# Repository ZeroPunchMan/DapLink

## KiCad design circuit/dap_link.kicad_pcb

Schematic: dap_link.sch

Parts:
C1: 10nF; C_0603_1608Metric_Pad1.05x0.95mm_HandSolder
C2: 100nF; C_0603_1608Metric_Pad1.05x0.95mm_HandSolder
C3: 1uF; C_0603_1608Metric_Pad1.05x0.95mm_HandSolder
C4, C7: 10pF; C_0603_1608Metric_Pad1.05x0.95mm_HandSolder
C5: 10uF; CP_EIA-3528-12_Kemet-T_Pad1.50x2.35mm_HandSolder
C6: 22uF; CP_EIA-3528-12_Kemet-T_Pad1.50x2.35mm_HandSolder
C8: 0.1uF; C_0603_1608Metric_Pad1.05x0.95mm_HandSolder
D1: LEDG; LED_0603_1608Metric_Pad1.05x0.95mm_HandSolder
D2: LEDR; LED_0603_1608Metric_Pad1.05x0.95mm_HandSolder
J1: USB_A_CONN; USB_A_CNCTech_1001-011-01101_Horizontal
J2: SWD_CONN_5P; PinHeader_1x05_P2.54mm_Vertical
J3: UART1_CONN_3P; PinHeader_1x03_P2.54mm_Vertical
J4: PAEX_CONN_8P; PinHeader_1x08_P2.54mm_Horizontal
R1: 1M; R_0603_1608Metric_Pad1.05x0.95mm_HandSolder
R2, R3: 22R; R_0603_1608Metric_Pad1.05x0.95mm_HandSolder
R4: 1.5K; R_0603_1608Metric_Pad1.05x0.95mm_HandSolder
R5: 0R; R_0603_1608Metric_Pad1.05x0.95mm_HandSolder
R6, R7: 100R; R_0603_1608Metric_Pad1.05x0.95mm_HandSolder
R8, R9, R11, R13, R14, R15, R16, R17, R18: 1K; R_0603_1608Metric_Pad1.05x0.95mm_HandSolder
R10, R12: 10K; R_0603_1608Metric_Pad1.05x0.95mm_HandSolder
U1: STM32F103CBTx; LQFP-48_7x7mm_P0.5mm
U2: AMS1117-3.3; SOT-223-3_TabPin2
Y1: 8MHz; Crystal_SMD_SeikoEpson_MC405-2Pin_9.6x4.1mm

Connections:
+3V3: C2.2, C3.2, C6.1, D1.2 (A), D2.2 (A), J2.5, R4.1, R10.1, U1.1 (VBAT), U1.9 (VDDA), U1.24 (VDD1), U1.36 (VDD2), U1.48 (VDD3), U2.2 (VO)
/LEDG_GPIO: R8.2, U1.29 (PA8)
/LEDR_GPIO: R9.2, U1.17 (PA7)
/NRST: C8.1, J2.4, R10.2, U1.7 (NRST)
/OSC_IN: C4.1, U1.5 (PD0/OSC_IN), Y1.1
/OSC_OUT: R5.1, U1.6 (PD1/OSC_OUT)
/PA0: R11.1, U1.10 (PA0)
/PA1: R13.1, U1.11 (PA1)
/PA2: R14.1, U1.12 (PA2)
/PA3: R15.1, U1.13 (PA3)
/PA4: R16.1, U1.14 (PA4)
/PA5: R17.1, U1.15 (PA5)
/PA6: R18.1, U1.16 (PA6)
/SWCLK: J2.2, U1.37 (PA14)
/SWDIO: J2.3, U1.34 (PA13)
/URX1: J3.2, R7.1
/USB_D+: R3.1, U1.33 (PA12)
/USB_D-: R2.1, U1.32 (PA11)
/UTX1: J3.3, R6.1
GND: C1.2, C2.1, C3.1, C4.2, C5.2, C6.2, C7.2, C8.2, J1.4 (GND), J2.1, J3.1, J4.1, R1.2, R12.2, U1.8 (VSSA), U1.23 (VSS1), U1.35 (VSS2), U1.47 (VSS3), U2.1 (GND)
unnamed: C1.1, J1.5 (Shield), R1.1
unnamed: C7.1, R5.2, Y1.2
unnamed: D1.1 (K), R8.1
unnamed: D2.1 (K), R9.1
unnamed: J1.2 (D-), R2.2
unnamed: J1.3 (D+), R3.2, R4.2
unnamed: J4.2, R18.2
unnamed: J4.3, R17.2
unnamed: J4.4, R16.2
unnamed: J4.5, R15.2
unnamed: J4.6, R14.2
unnamed: J4.7, R13.2
unnamed: J4.8, R11.2
unnamed: R6.2, U1.30 (PA9)
unnamed: R7.2, U1.31 (PA10)
unnamed: R12.1, U1.44 (BOOT0)

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
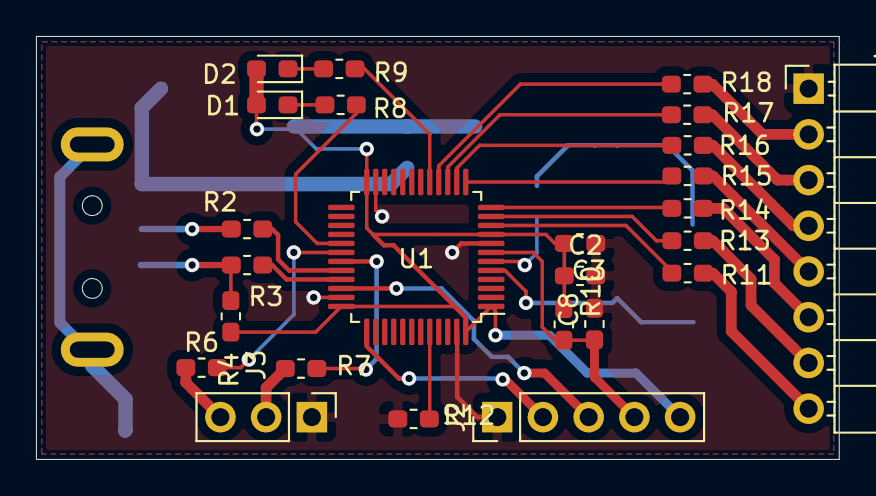
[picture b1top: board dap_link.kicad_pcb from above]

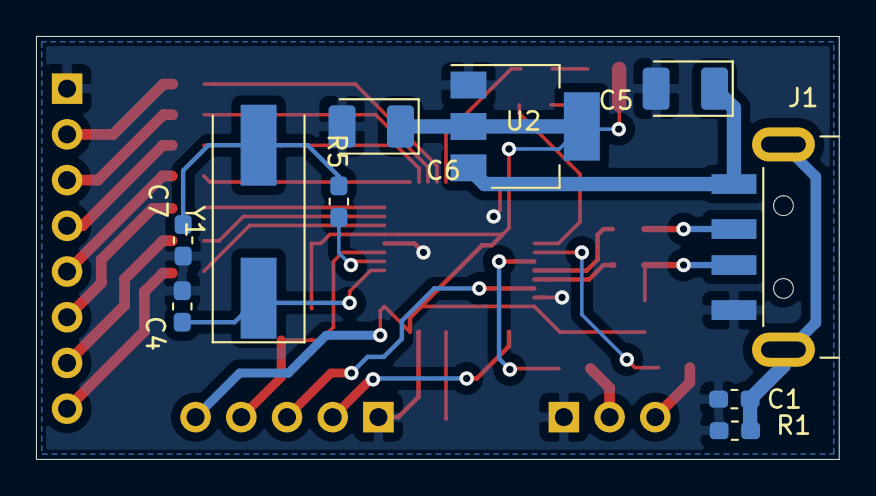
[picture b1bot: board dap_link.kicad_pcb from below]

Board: 2 copper layers, 44.6 x 23.5 mm, 35 parts (10 on the bottom side), 37 nets.

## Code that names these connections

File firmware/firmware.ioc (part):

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Mcu.Name=STM32F103C(8-B)Tx
Mcu.Package=LQFP48
Mcu.UserName=STM32F103C8Tx
PA10.Mode=Asynchronous
PA10.Signal=USART1_RX
PA13.Mode=Serial_Wire
PA13.Signal=SYS_JTMS-SWDIO
PA14.Mode=Serial_Wire
PA14.Signal=SYS_JTCK-SWCLK
PA7.Signal=GPIO_Output
PA8.Signal=GPIO_Output
PA9.Mode=Asynchronous
PA9.Signal=USART1_TX
PD0-OSC_IN.Mode=HSE-External-Oscillator
PD0-OSC_IN.Signal=RCC_OSC_IN
PD1-OSC_OUT.Mode=HSE-External-Oscillator
PD1-OSC_OUT.Signal=RCC_OSC_OUT
RCC.SYSCLKFreq_VALUE=48000000
RCC.SYSCLKSource=RCC_SYSCLKSOURCE_PLLCLK
board=custom

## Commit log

2020-03-22 footprint done
2020-03-22 erc ok
2020-03-25 DA111
2020-03-30 1333
2020-03-30 pcb almost done
2020-03-30 ready to print
2020-03-30 change wire width to connector
2020-03-31 pcb done
2020-04-08 cubemx project added
2020-04-09 jtag port error
2020-04-09 led ok
2020-04-09 download ok
2020-04-11 debug ok
2020-04-11 remove build files
2020-04-11 makefile will detect os
2020-04-11 windows不能使用旧版控制台
2020-04-13 gdb add cd command
2020-04-13 openocd in pipe
2020-04-14 makefile
2020-04-14 systick ok; usart not full tested
2020-04-18 resolve warnings
2020-04-18 usart warning
2020-04-29 debug log redirect
2020-05-13 dap source files added
2020-05-14 dap config, not tested
2020-07-10 libraries configuration
2020-07-12 lis3dh spi movement detect
2020-12-15 lib update
